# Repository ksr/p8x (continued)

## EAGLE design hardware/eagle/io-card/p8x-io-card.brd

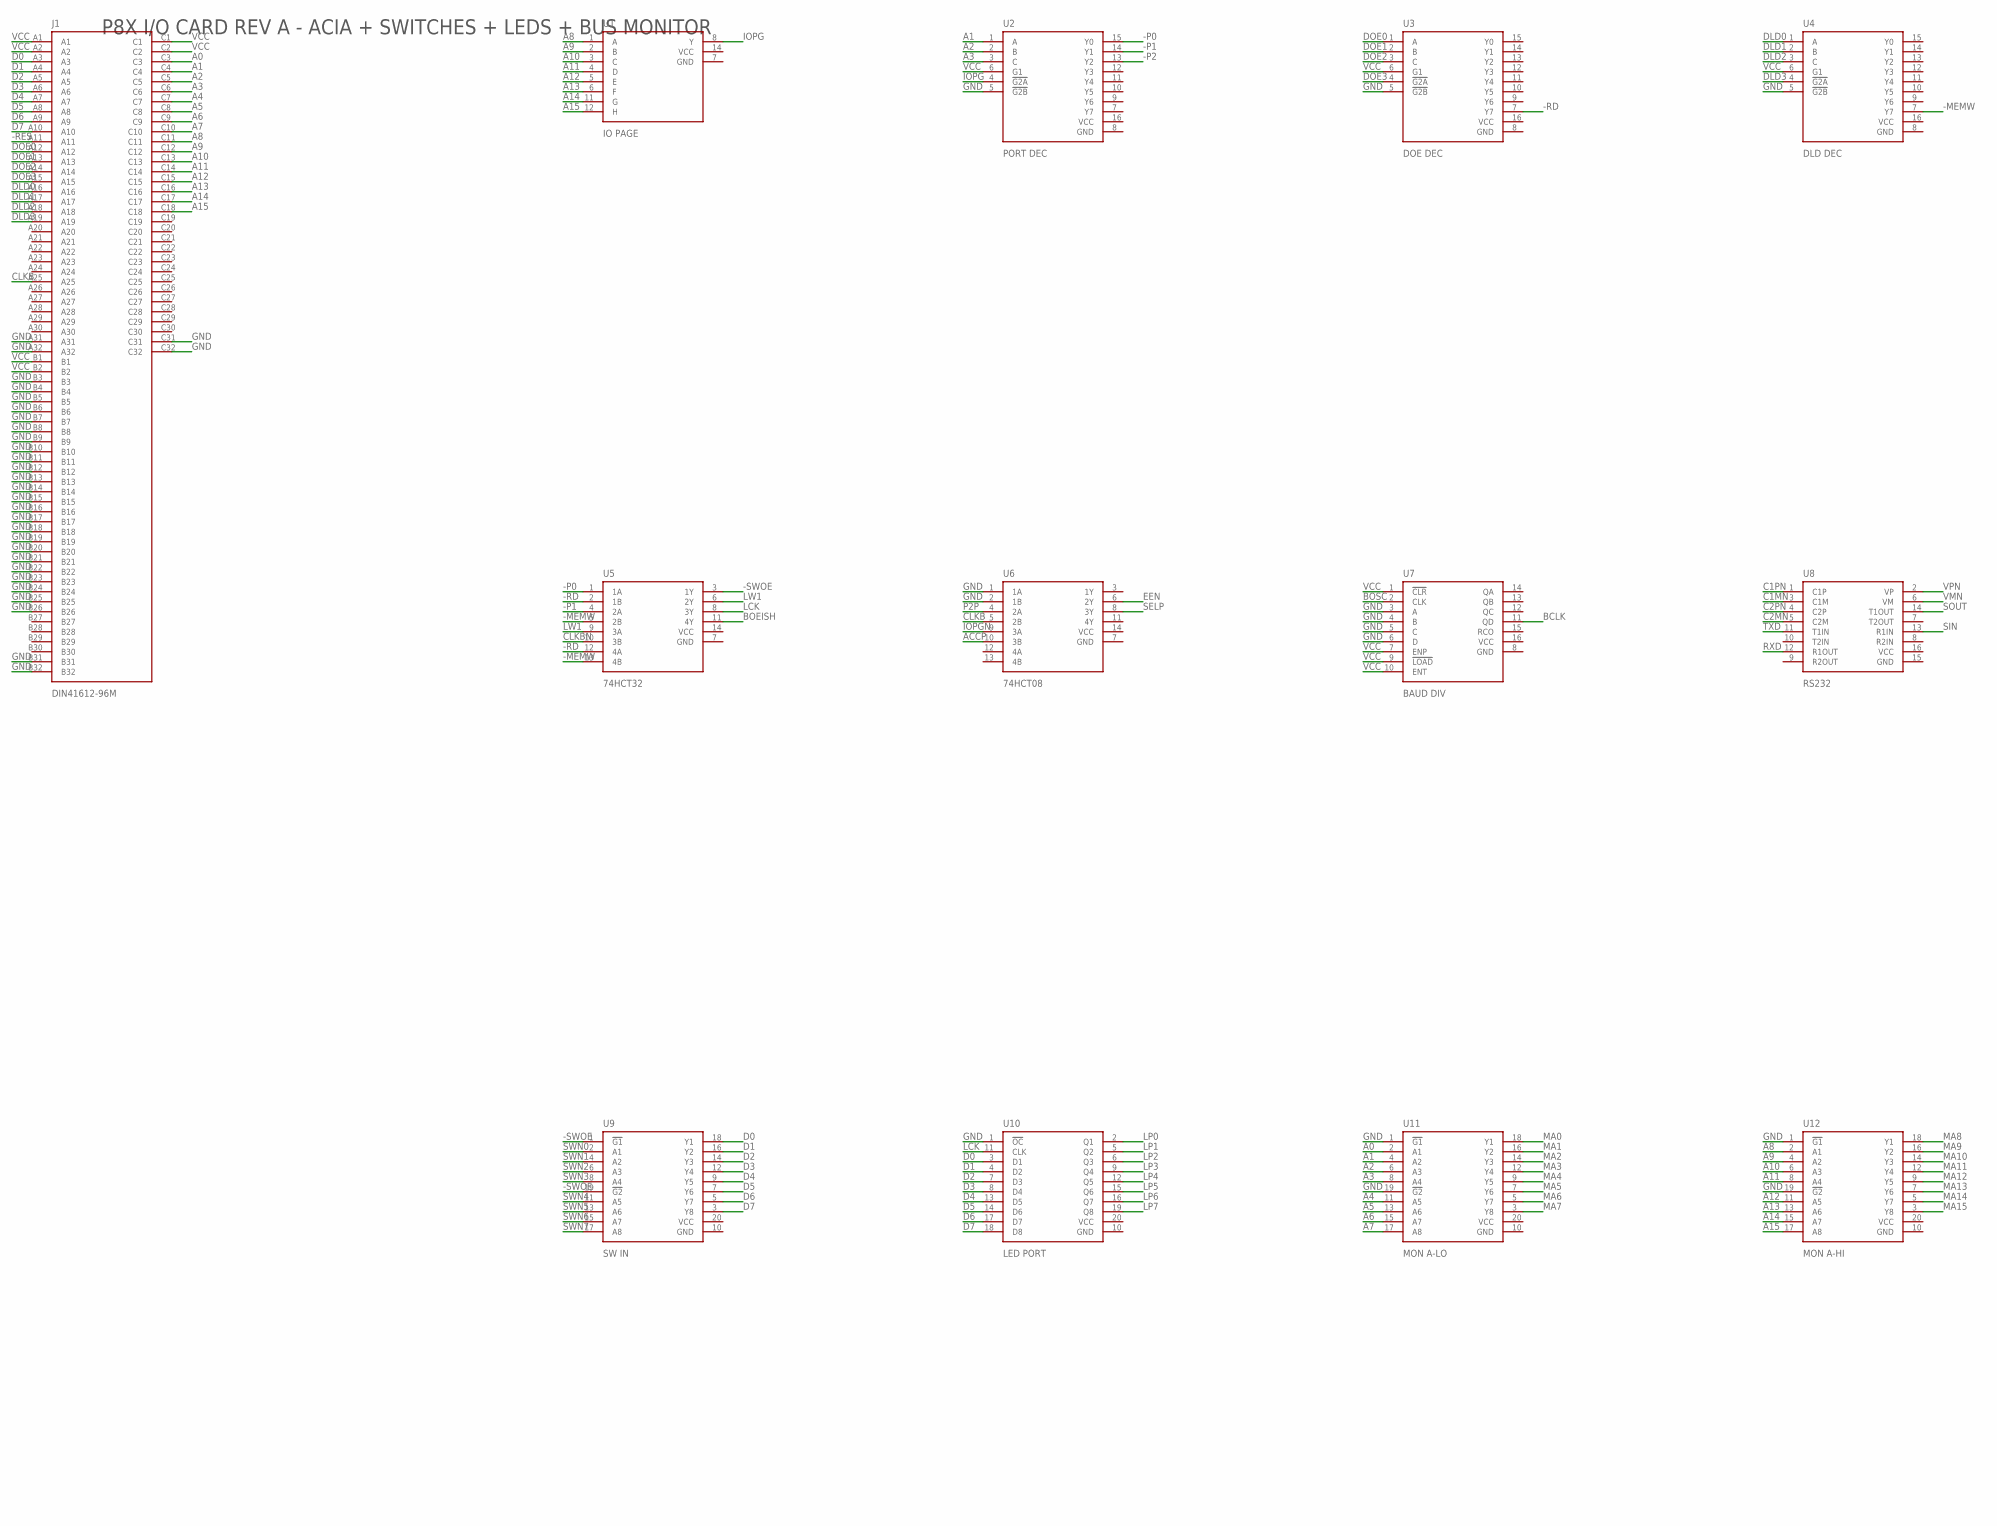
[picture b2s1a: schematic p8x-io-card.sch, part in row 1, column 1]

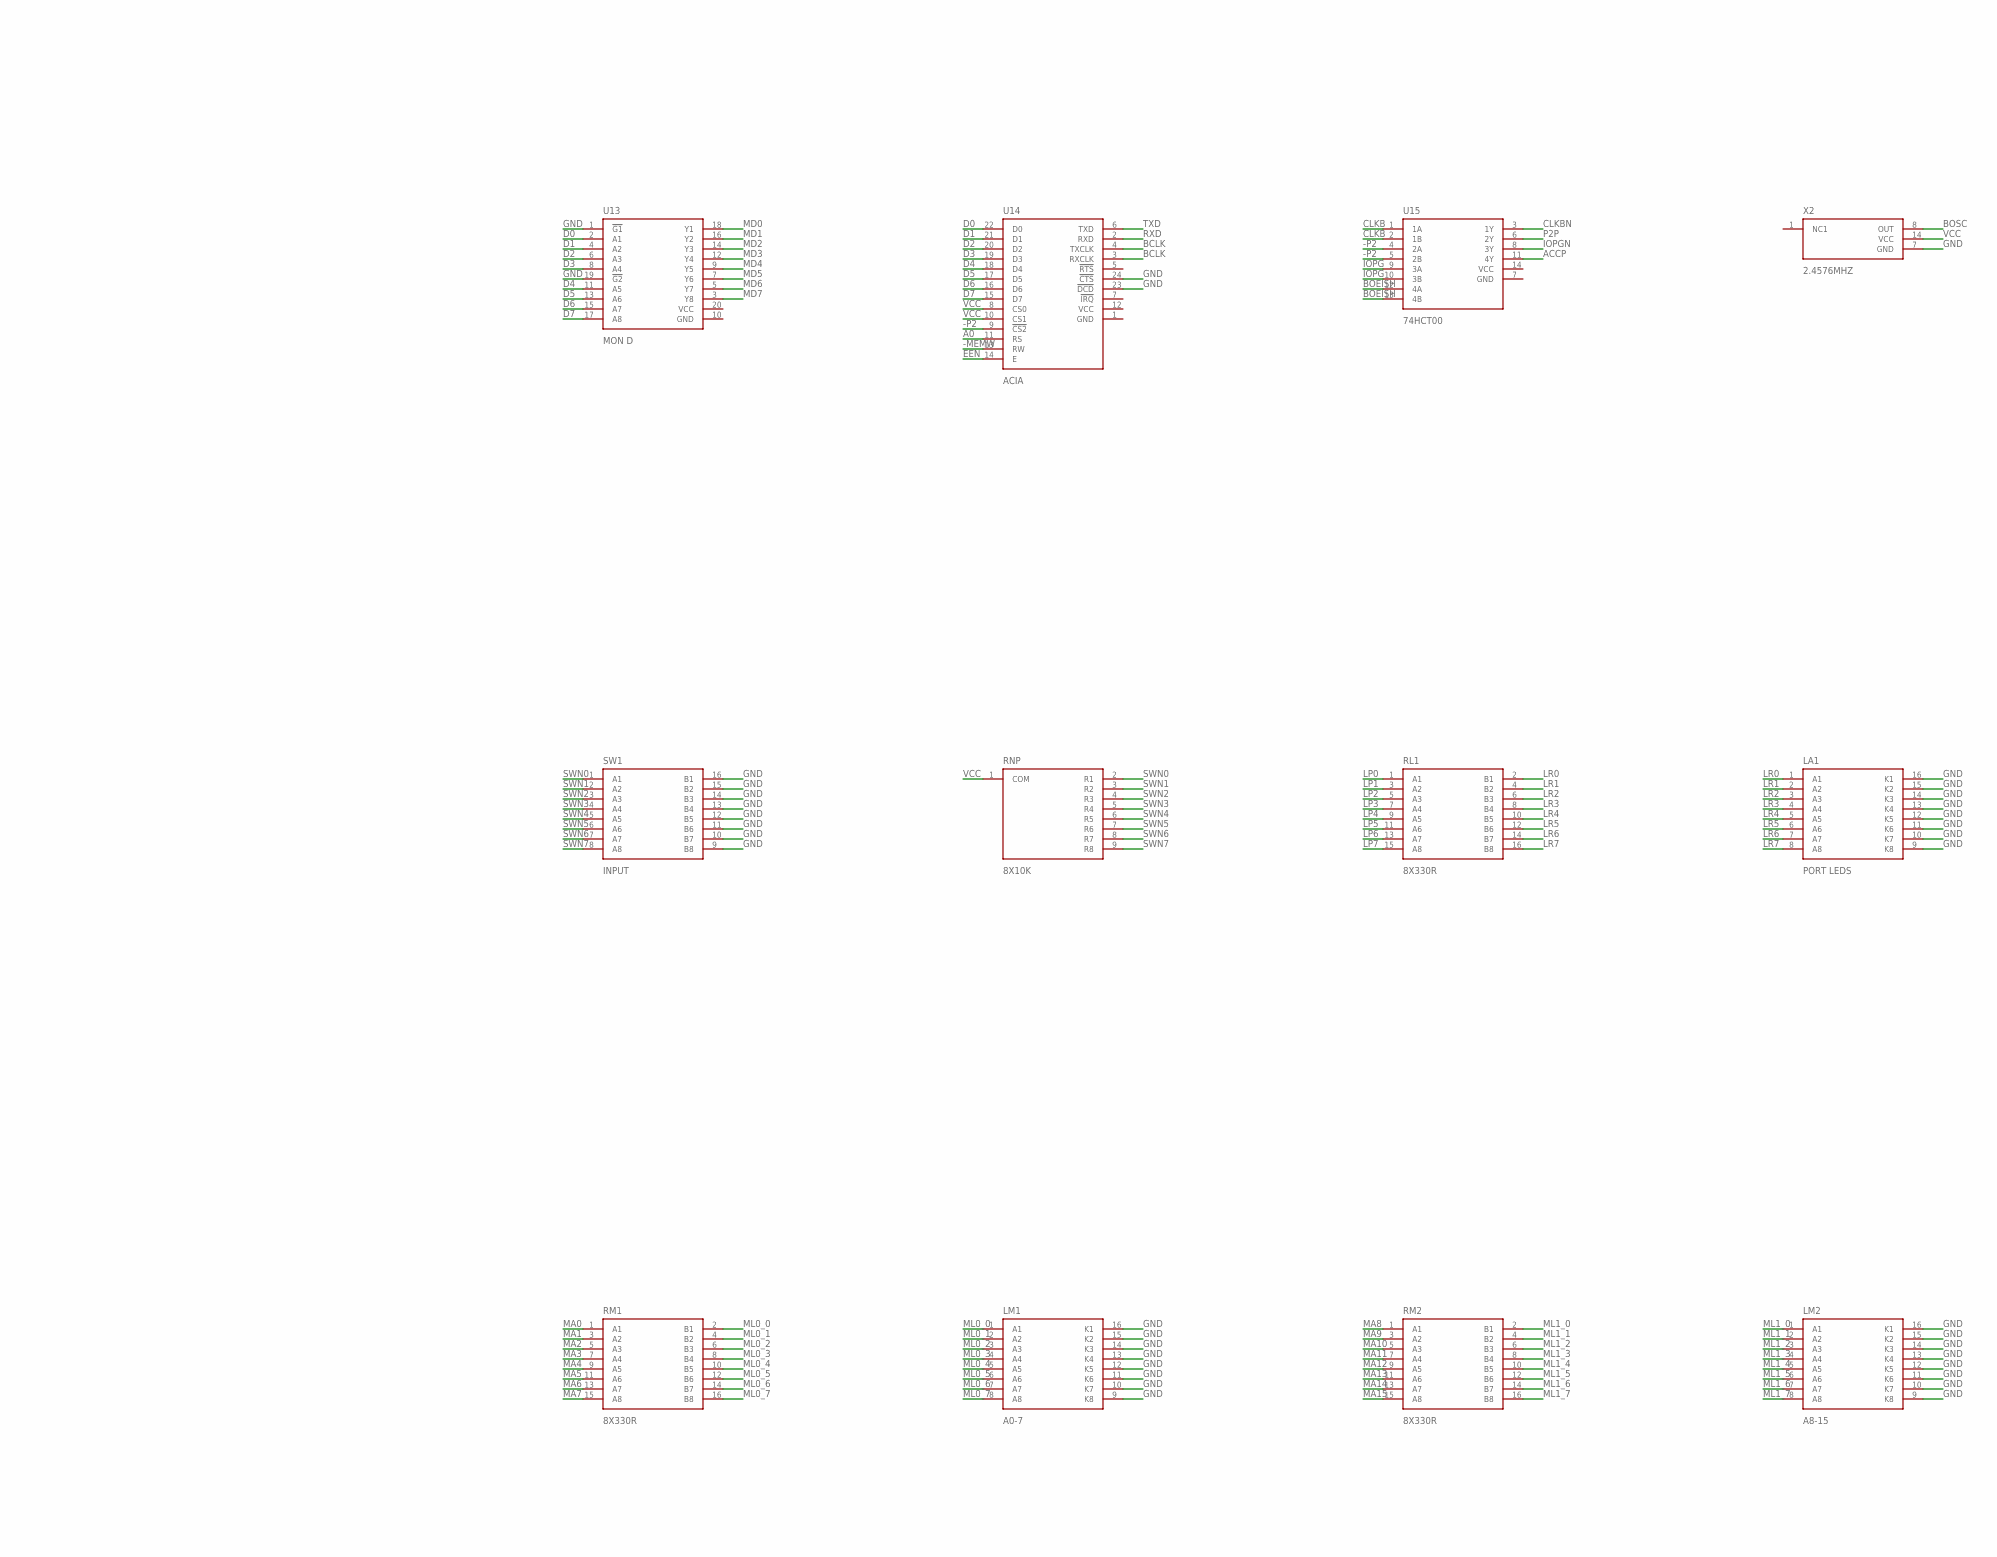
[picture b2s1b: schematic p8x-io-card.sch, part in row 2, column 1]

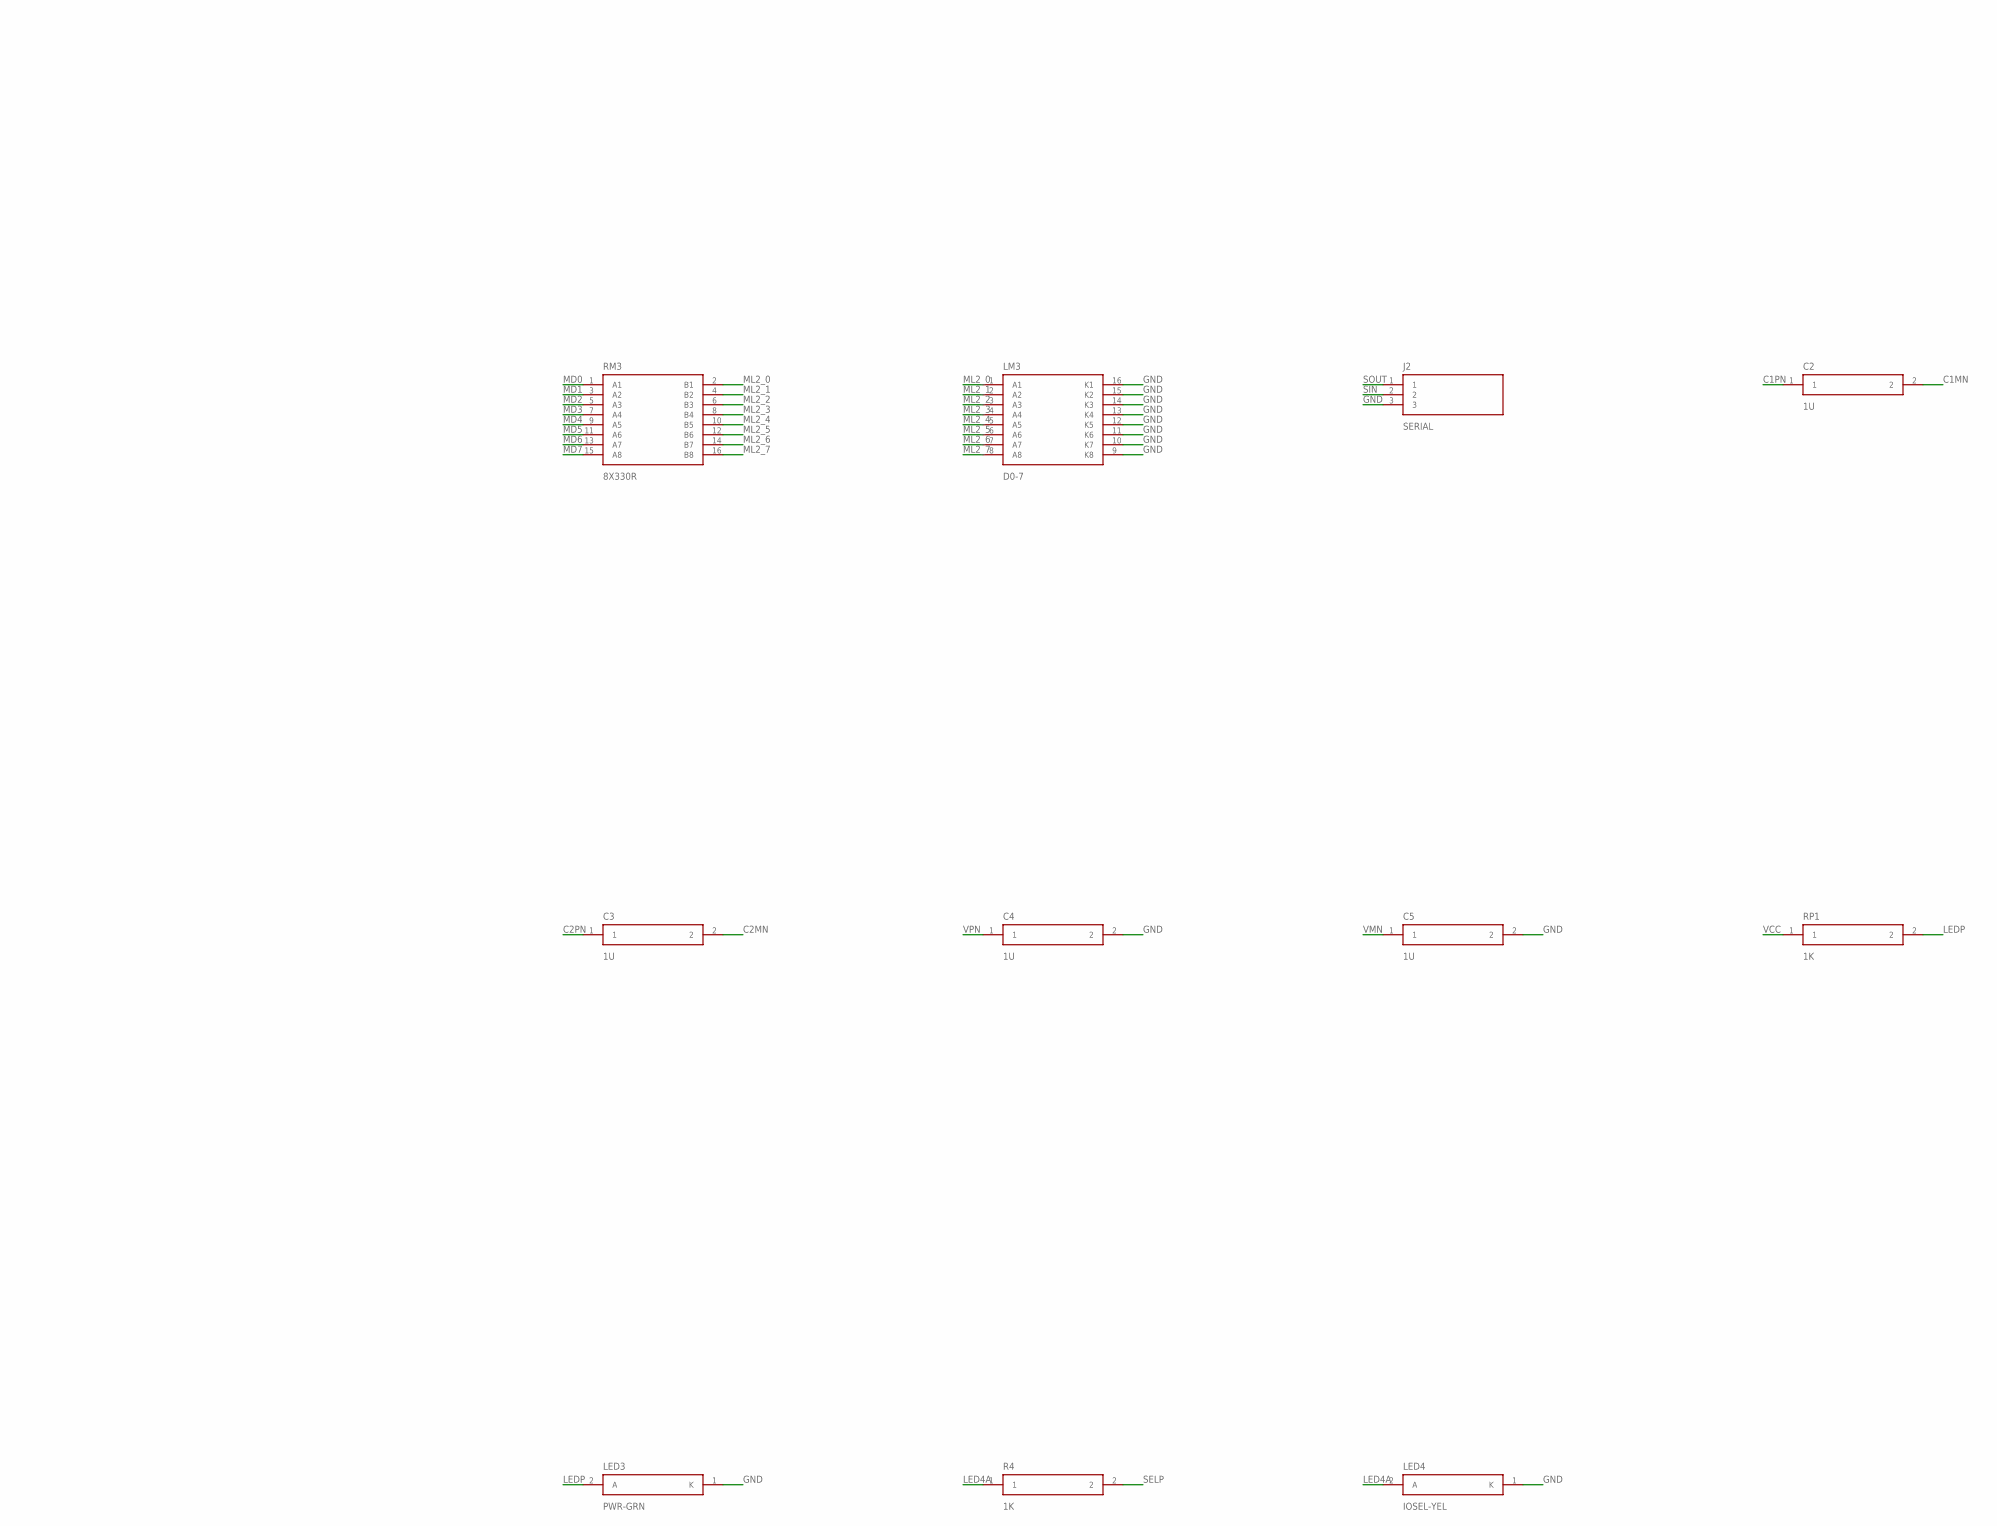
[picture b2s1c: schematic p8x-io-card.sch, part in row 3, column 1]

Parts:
C2, C3, C4, C5: 1U; C_DISC
J1: DIN41612-96M; DIN96
J2: SERIAL; HDR3
LA1: PORT LEDS; DIP16
LED3: PWR-GRN; LED5
LED4: IOSEL-YEL; LED5
LM1: A0-7; DIP16
LM2: A8-15; DIP16
LM3: D0-7; DIP16
R4: 1K; R_AXIAL
RL1: 8X330R; SIP16
RM1, RM2, RM3: 8X330R; SIP16
RNP: 8X10K; SIP9
RP1: 1K; R_AXIAL
SW1: INPUT; DIP16
U1: IO PAGE; DIP14
U2: PORT DEC; DIP16
U3: DOE DEC; DIP16
U4: DLD DEC; DIP16
U5: 74HCT32; DIP14
U6: 74HCT08; DIP14
U7: BAUD DIV; DIP16
U8: RS232; DIP16
U9: SW IN; DIP20
U10: LED PORT; DIP20
U11: MON A-LO; DIP20
U12: MON A-HI; DIP20
U13: MON D; DIP20
U14: ACIA; DIP24W
U15: 74HCT00; DIP14
X2: 2.4576MHZ; OSC4

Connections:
-MEMW: U4.7 (Y7), U5.5 (2B), U5.13 (4B), U14.13 (RW)
-P0: U2.15 (Y0), U5.1 (1A)
-P1: U2.14 (Y1), U5.4 (2A)
-P2: U2.13 (Y2), U14.9 (!CS2), U15.4 (2A), U15.5 (2B)
-RD: U3.7 (Y7), U5.2 (1B), U5.12 (4A)
-RES: J1.A11
-SWOE: U5.3 (1Y), U9.1 (!G1), U9.19 (!G2)
A0: J1.C3, U11.2 (A1), U14.11 (RS)
A1: J1.C4, U2.1 (A), U11.4 (A2)
A2: J1.C5, U2.2 (B), U11.6 (A3)
A3: J1.C6, U2.3 (C), U11.8 (A4)
A4: J1.C7, U11.11 (A5)
A5: J1.C8, U11.13 (A6)
A6: J1.C9, U11.15 (A7)
A7: J1.C10, U11.17 (A8)
A8: J1.C11, U1.1 (A), U12.2 (A1)
A9: J1.C12, U1.2 (B), U12.4 (A2)
A10: J1.C13, U1.3 (C), U12.6 (A3)
A11: J1.C14, U1.4 (D), U12.8 (A4)
A12: J1.C15, U1.5 (E), U12.11 (A5)
A13: J1.C16, U1.6 (F), U12.13 (A6)
A14: J1.C17, U1.11 (G), U12.15 (A7)
A15: J1.C18, U1.12 (H), U12.17 (A8)
ACCP: U6.10 (3B), U15.11 (4Y)
BCLK: U7.11 (QD), U14.3 (RXCLK), U14.4 (TXCLK)
BOEISH: U5.11 (4Y), U15.12 (4A), U15.13 (4B)
BOSC: U7.2 (CLK), X2.8 (OUT)
C1MN: C2.2, U8.3 (C1M)
C1PN: C2.1, U8.1 (C1P)
C2MN: C3.2, U8.5 (C2M)
C2PN: C3.1, U8.4 (C2P)
CLKB: J1.A25, U6.5 (2B), U15.1 (1A), U15.2 (1B)
CLKBN: U5.10 (3B), U15.3 (1Y)
D0: J1.A3, U9.18 (Y1), U10.3 (D1), U13.2 (A1), U14.22 (D0)
D1: J1.A4, U9.16 (Y2), U10.4 (D2), U13.4 (A2), U14.21 (D1)
D2: J1.A5, U9.14 (Y3), U10.7 (D3), U13.6 (A3), U14.20 (D2)
D3: J1.A6, U9.12 (Y4), U10.8 (D4), U13.8 (A4), U14.19 (D3)
D4: J1.A7, U9.9 (Y5), U10.13 (D5), U13.11 (A5), U14.18 (D4)
D5: J1.A8, U9.7 (Y6), U10.14 (D6), U13.13 (A6), U14.17 (D5)
D6: J1.A9, U9.5 (Y7), U10.17 (D7), U13.15 (A7), U14.16 (D6)
D7: J1.A10, U9.3 (Y8), U10.18 (D8), U13.17 (A8), U14.15 (D7)
DLD0: J1.A16, U4.1 (A)
DLD1: J1.A17, U4.2 (B)
DLD2: J1.A18, U4.3 (C)
DLD3: J1.A19, U4.4 (!G2A)
DOE0: J1.A12, U3.1 (A)
DOE1: J1.A13, U3.2 (B)
DOE2: J1.A14, U3.3 (C)
DOE3: J1.A15, U3.4 (!G2A)
EEN: U6.6 (2Y), U14.14 (E)
GND: C4.2, C5.2, J1.A31, J1.A32, J1.B3, J1.B4, J1.B5, J1.B6, J1.B7, J1.B8, J1.B9, J1.B10, J1.B11, J1.B12, J1.B13, J1.B14, J1.B15, J1.B16, J1.B17, J1.B18, J1.B19, J1.B20, J1.B21, J1.B22, J1.B23, J1.B24, J1.B25, J1.B26, J1.B31, J1.B32, J1.C31, J1.C32, J2.3, LA1.9 (K8), LA1.10 (K7), LA1.11 (K6), LA1.12 (K5), LA1.13 (K4), LA1.14 (K3), LA1.15 (K2), LA1.16 (K1), LED3.1 (K), LED4.1 (K), LM1.9 (K8), LM1.10 (K7), LM1.11 (K6), LM1.12 (K5), LM1.13 (K4), LM1.14 (K3), LM1.15 (K2), LM1.16 (K1), LM2.9 (K8), LM2.10 (K7), LM2.11 (K6), LM2.12 (K5), LM2.13 (K4), LM2.14 (K3), LM2.15 (K2), LM2.16 (K1), LM3.9 (K8), LM3.10 (K7), LM3.11 (K6), LM3.12 (K5), LM3.13 (K4), LM3.14 (K3), LM3.15 (K2), LM3.16 (K1), SW1.9 (B8), SW1.10 (B7), SW1.11 (B6), SW1.12 (B5), SW1.13 (B4), SW1.14 (B3), SW1.15 (B2), SW1.16 (B1), U2.5 (!G2B), U3.5 (!G2B), U4.5 (!G2B), U6.1 (1A), U6.2 (1B), U7.3 (A), U7.4 (B), U7.5 (C), U7.6 (D), U10.1 (!OC), U11.1 (!G1), U11.19 (!G2), U12.1 (!G1), U12.19 (!G2), U13.1 (!G1), U13.19 (!G2), U14.23 (!DCD), U14.24 (!CTS), X2.7 (GND)
IOPG: U1.8 (Y), U2.4 (!G2A), U15.9 (3A), U15.10 (3B)
IOPGN: U6.9 (3A), U15.8 (3Y)
LCK: U5.8 (3Y), U10.11 (CLK)
LED4A: LED4.2 (A), R4.1
LEDP: LED3.2 (A), RP1.2
LP0: RL1.1 (A1), U10.2 (Q1)
LP1: RL1.3 (A2), U10.5 (Q2)
LP2: RL1.5 (A3), U10.6 (Q3)
LP3: RL1.7 (A4), U10.9 (Q4)
LP4: RL1.9 (A5), U10.12 (Q5)
LP5: RL1.11 (A6), U10.15 (Q6)
LP6: RL1.13 (A7), U10.16 (Q7)
LP7: RL1.15 (A8), U10.19 (Q8)
LR0: LA1.1 (A1), RL1.2 (B1)
LR1: LA1.2 (A2), RL1.4 (B2)
LR2: LA1.3 (A3), RL1.6 (B3)
LR3: LA1.4 (A4), RL1.8 (B4)
LR4: LA1.5 (A5), RL1.10 (B5)
LR5: LA1.6 (A6), RL1.12 (B6)
LR6: LA1.7 (A7), RL1.14 (B7)
LR7: LA1.8 (A8), RL1.16 (B8)
LW1: U5.6 (2Y), U5.9 (3A)
MA0: RM1.1 (A1), U11.18 (Y1)
MA1: RM1.3 (A2), U11.16 (Y2)
MA2: RM1.5 (A3), U11.14 (Y3)
MA3: RM1.7 (A4), U11.12 (Y4)
MA4: RM1.9 (A5), U11.9 (Y5)
MA5: RM1.11 (A6), U11.7 (Y6)
MA6: RM1.13 (A7), U11.5 (Y7)
MA7: RM1.15 (A8), U11.3 (Y8)
MA8: RM2.1 (A1), U12.18 (Y1)
MA9: RM2.3 (A2), U12.16 (Y2)
MA10: RM2.5 (A3), U12.14 (Y3)
MA11: RM2.7 (A4), U12.12 (Y4)
MA12: RM2.9 (A5), U12.9 (Y5)
MA13: RM2.11 (A6), U12.7 (Y6)
MA14: RM2.13 (A7), U12.5 (Y7)
MA15: RM2.15 (A8), U12.3 (Y8)
MD0: RM3.1 (A1), U13.18 (Y1)
MD1: RM3.3 (A2), U13.16 (Y2)
MD2: RM3.5 (A3), U13.14 (Y3)
MD3: RM3.7 (A4), U13.12 (Y4)
MD4: RM3.9 (A5), U13.9 (Y5)
MD5: RM3.11 (A6), U13.7 (Y6)
MD6: RM3.13 (A7), U13.5 (Y7)
MD7: RM3.15 (A8), U13.3 (Y8)
ML0_0: LM1.1 (A1), RM1.2 (B1)
ML0_1: LM1.2 (A2), RM1.4 (B2)
ML0_2: LM1.3 (A3), RM1.6 (B3)
ML0_3: LM1.4 (A4), RM1.8 (B4)
ML0_4: LM1.5 (A5), RM1.10 (B5)
ML0_5: LM1.6 (A6), RM1.12 (B6)
ML0_6: LM1.7 (A7), RM1.14 (B7)
ML0_7: LM1.8 (A8), RM1.16 (B8)
ML1_0: LM2.1 (A1), RM2.2 (B1)
ML1_1: LM2.2 (A2), RM2.4 (B2)
ML1_2: LM2.3 (A3), RM2.6 (B3)
ML1_3: LM2.4 (A4), RM2.8 (B4)
ML1_4: LM2.5 (A5), RM2.10 (B5)
ML1_5: LM2.6 (A6), RM2.12 (B6)
ML1_6: LM2.7 (A7), RM2.14 (B7)
ML1_7: LM2.8 (A8), RM2.16 (B8)
ML2_0: LM3.1 (A1), RM3.2 (B1)
ML2_1: LM3.2 (A2), RM3.4 (B2)
ML2_2: LM3.3 (A3), RM3.6 (B3)
ML2_3: LM3.4 (A4), RM3.8 (B4)
ML2_4: LM3.5 (A5), RM3.10 (B5)
ML2_5: LM3.6 (A6), RM3.12 (B6)
ML2_6: LM3.7 (A7), RM3.14 (B7)
ML2_7: LM3.8 (A8), RM3.16 (B8)
P2P: U6.4 (2A), U15.6 (2Y)
RXD: U8.12 (R1OUT), U14.2 (RXD)
SELP: R4.2, U6.8 (3Y)
SIN: J2.2, U8.13 (R1IN)
SOUT: J2.1, U8.14 (T1OUT)
SWN0: RNP.2 (R1), SW1.1 (A1), U9.2 (A1)
SWN1: RNP.3 (R2), SW1.2 (A2), U9.4 (A2)
SWN2: RNP.4 (R3), SW1.3 (A3), U9.6 (A3)
SWN3: RNP.5 (R4), SW1.4 (A4), U9.8 (A4)
SWN4: RNP.6 (R5), SW1.5 (A5), U9.11 (A5)
SWN5: RNP.7 (R6), SW1.6 (A6), U9.13 (A6)
SWN6: RNP.8 (R7), SW1.7 (A7), U9.15 (A7)
SWN7: RNP.9 (R8), SW1.8 (A8), U9.17 (A8)
TXD: U8.11 (T1IN), U14.6 (TXD)
VCC: J1.A1, J1.A2, J1.B1, J1.B2, J1.C1, J1.C2, RNP.1 (COM), RP1.1, U2.6 (G1), U3.6 (G1), U4.6 (G1), U7.1 (!CLR), U7.7 (ENP), U7.9 (!LOAD), U7.10 (ENT), U14.8 (CS0), U14.10 (CS1), X2.14 (VCC)
VMN: C5.1, U8.6 (VM)
VPN: C4.1, U8.2 (VP)

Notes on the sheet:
P8X I/O CARD REV A - ACIA + SWITCHES + LEDS + BUS MONITOR

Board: 4 copper layers, 36 parts (0 on the bottom side), 137 nets, no tracks yet.
